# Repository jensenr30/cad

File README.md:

# Ryan's CAD Files (Schematics, PCBs, Simulations)

## kicad5
I started using KiCad 5.1.2 to draw schematics and lay out PCBs in May 2019.

## kicad4
I used KiCad 4.0.6 for 3 weeks in September 2017. The two projects I completed are:
* [Shift-Register Break-Out-Board](/kicad4/SRBOB) - A modular daisy-chain-able serial-in-parallel-out 74hc595-based shift register circuit board.
* [XPhone Input Board](/kicad4/XPhone/Input_Board) - A quad transducer amplifier and glockenspiel-key-hit-detection circuit board.

## eagle6
Eagle was the first CAD program I ever used. I started using Eagle (on version 5.11.0) sometime in early 2011. I stopped on version 6.6.0 in mid 2017.  Some of the more interesting projects I completed using Eagle are:
* [Analog Synth](eagle6/Analog%20Synth) - a bunch of analog (and digital) DIY synth modules.  Designed, built, and tested by your truly.  This includes VCOs, VCFs, VCAs, sequencers, front-panel designs, digital delay, manual oscillators, and power-distribution interconnect PCBs.
* [Stroboscope](eagle6/Stroboscope) - a device that can turn on and off LEDs very fast (at audio frequencies) in order to produce interesting/useful/helpful visual effects.  A stroboscope can be used to enable a human to monitor the rotation of things in real time, e.g. fans, drills, wheels, motors, spinning objects, guitar strings, and any other object engaged in cyclic motion.
* [VU Meter](eagle6/VU%20meter) - a circuit that represents audio amplitude vertically on several bargraphs (each bargraph displays the amplitude of a given section of the audio spectrum).  The device can be used to build a real-time visual audio spectrum analyzer.
* [FreqCount84](eagle6/FreqCount84) - Atmel microcontroller-based design for precise measurement of frequency of square waves.  I believe the hwardware & firmware achieved an accuracy of ± a few ppm with the help of a 1.5 pm TCXO.
* [9x9 LED Matrix](eagle6/9x9%20LED%20Matrix) - a 2D array of LEDs (9 LEDs wide, 9 LEDs tall).  I remember wanting to build an array that had an odd number of pixels because it would allow me to make symetric visual displays.  I programmed a game of pong for this 9x9 LED Matrix.  That code exists in [my repo for Arduino programs](https://github.com/jensenr30/Arduino/tree/master/_DISPLAY/9x9_LED_Matrix).
* [Prototype Boards](eagle6/Prototype%20Boards) - three PCBs that enable DIY circuit construction.  0.1"-arrays of SMD pads, 0.1"-arrays of through-holes, SOT-to-DIP break-out-boards, SOIC-to-DIP break-out-boards, etc...

## LTspice IV
I have used [LTspice](https://en.wikipedia.org/wiki/LTspice) version IV to simulate some of my circuits.

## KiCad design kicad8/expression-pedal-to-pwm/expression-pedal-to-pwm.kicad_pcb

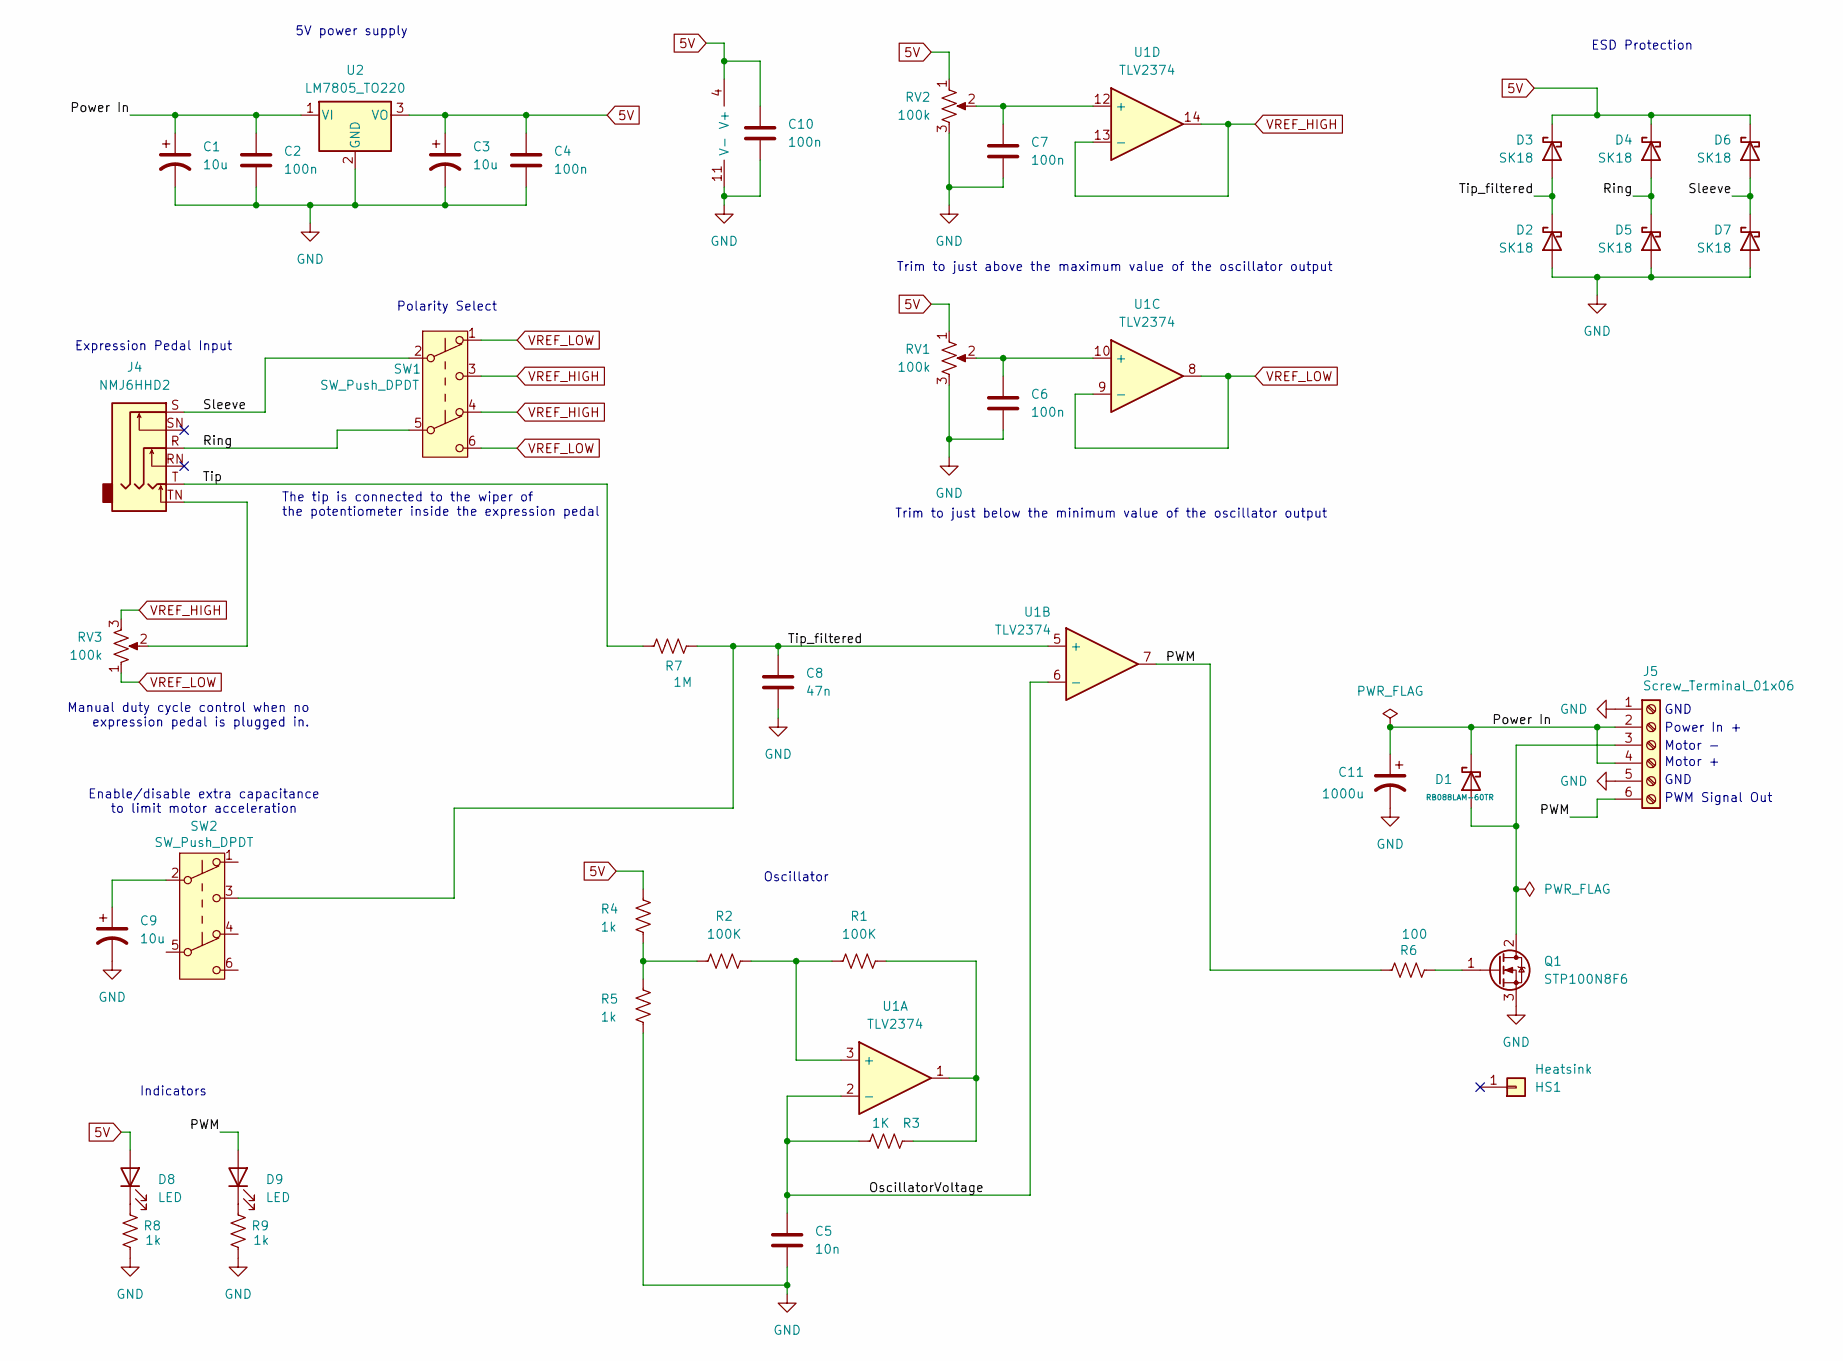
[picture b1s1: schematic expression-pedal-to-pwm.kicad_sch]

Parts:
C1, C3, C9: 10u; CP_Radial_D5.0mm_P2.50mm
C2, C4, C6, C7, C10: 100n; C_0603_1608Metric_Pad1.08x0.95mm_HandSolder
C5: 10n; C_0603_1608Metric_Pad1.08x0.95mm_HandSolder
C8: 47n; C_0603_1608Metric_Pad1.08x0.95mm_HandSolder
C11: 1000u; CP_Radial_D10.0mm_P5.00mm
D1: RB088LAM-60TR; D_SOD-128
D2, D3, D4, D5, D6, D7: SK18; D_SMA
D8, D9: LED; LED_D3.0mm_Horizontal_O3.81mm_Z6.0mm
HS1: Heatsink; Heatsink_Fischer_SK104-STCB_35x13mm__2xDrill3.5mm_ScrewM3
J4: NMJ6HHD2; Jack_6.35mm_Neutrik_NMJ6HHD2_Horizontal
J5: Screw_Terminal_01x06; TerminalBlock_MetzConnect_Type086_RT03406HBLC_1x06_P3.81mm_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
Q1: STP100N8F6; TO-220-3_Vertical
R1, R2: 100K; R_0603_1608Metric_Pad0.98x0.95mm_HandSolder
R3: 1K; R_0603_1608Metric_Pad0.98x0.95mm_HandSolder
R4, R5, R8, R9: 1k; R_0603_1608Metric_Pad0.98x0.95mm_HandSolder
R6: 100; R_0603_1608Metric_Pad0.98x0.95mm_HandSolder
R7: 1M; R_0603_1608Metric_Pad0.98x0.95mm_HandSolder
RV1, RV2: 100k; Potentiometer_Bourns_3296W_Vertical
RV3: 100k; Potentiometer_Piher_T-16H_Single_Horizontal
SW1, SW2: SW_Push_DPDT; SW_E-Switch_EG2219_DPDT_Angled
U1: TLV2374; SOIC-14_3.9x8.7mm_P1.27mm
U2: LM7805_TO220; TO-220-3_Vertical

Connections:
5V: C3.1, C4.1, C10.1, D3.1 (K), D4.1 (K), D6.1 (K), D8.2 (A), R4.2, RV1.1, RV2.1, U1.4 (V+), U2.3 (VO)
/OscillatorVoltage: C5.1, R3.2, U1.2 (-), U1.6 (-)
/PWM: D9.2 (A), J5.6, R6.1, U1.7
/Power In: C1.1, C2.1, C11.1, D1.1 (K), J5.2, J5.4, U2.1 (VI)
/Ring: D4.2 (A), D5.1 (K), J4.R, SW1.5 (B)
/Sleeve: D6.2 (A), D7.1 (K), J4.S, SW1.2 (B)
/Tip: J4.T, R7.2
/Tip_filtered: C8.1, D2.1 (K), D3.2 (A), R7.1, SW2.3 (C), U1.5 (+)
GND: C1.2, C2.2, C3.2, C4.2, C5.2, C6.2, C7.2, C8.2, C9.2, C10.2, C11.2, D2.2 (A), D5.2 (A), D7.2 (A), J5.1, J5.5, Q1.3 (S), R5.1, R8.1, R9.1, RV1.3, RV2.3, U1.11 (V-), U2.2 (GND)
unnamed: C9.1, SW2.2 (B)
unnamed: D1.2 (A), J5.3, Q1.2 (D)
unnamed: D8.1 (K), R8.2
unnamed: D9.1 (K), R9.2
unnamed: J4.TN, RV3.2
unnamed: Q1.1 (G), R6.2
unnamed: R1.2, R3.1, U1.1
unnamed: R2.1, R4.1, R5.2
unnamed: R1.1, R2.2, U1.3 (+)
unnamed: C6.1, RV1.2, U1.10 (+)
unnamed: C7.1, RV2.2, U1.12 (+)
VREF_HIGH: RV3.3, SW1.3 (C), SW1.4 (A), U1.13 (-), U1.14
VREF_LOW: RV3.1, SW1.1 (A), SW1.6 (C), U1.8, U1.9 (-)

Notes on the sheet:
ESD Protection
The tip is connected to the wiper of the potentiometer inside the expression pedal
GND
Power In +
Manual duty cycle control when no expression pedal is plugged in.
5V power supply
Indicators
Motor -
Motor +
Oscillator
Expression Pedal Input
PWM Signal Out
Trim to just above the maximum value of the oscillator output
Trim to just below the minimum value of the oscillator output
Polarity Select
Enable/disable extra capacitance to limit motor acceleration

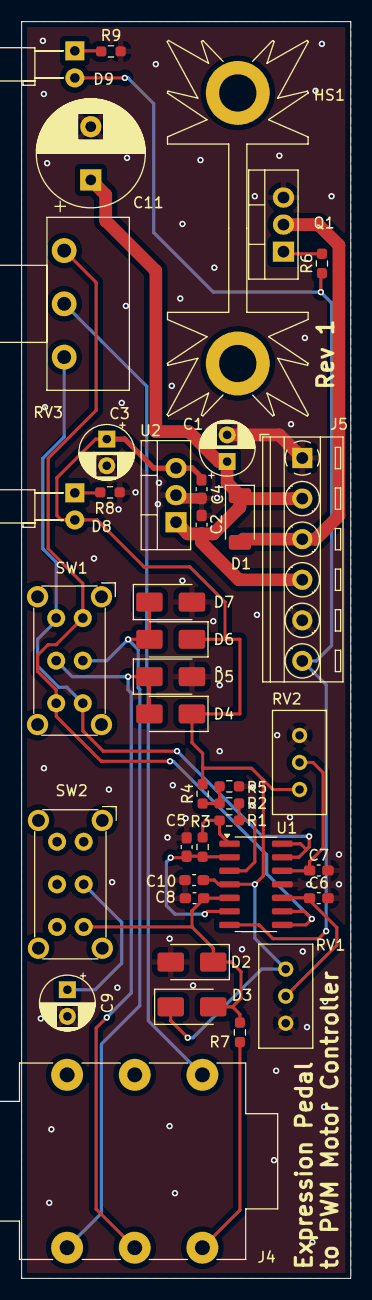
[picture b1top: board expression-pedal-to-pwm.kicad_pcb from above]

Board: 2 copper layers, 30.9 x 118.0 mm, 40 parts (0 on the bottom side), 22 nets.

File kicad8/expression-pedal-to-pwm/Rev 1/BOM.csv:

"Reference","Value","Datasheet","Footprint","Qty","DNP"
"C1  C3  C9","10u","~","Capacitor_THT:CP_Radial_D5.0mm_P2.50mm","3",""
"C2  C4  C6  C7  C10","100n","~","Capacitor_SMD:C_0603_1608Metric_Pad1.08x0.95mm_HandSolder","5",""
"C5","10n","~","Capacitor_SMD:C_0603_1608Metric_Pad1.08x0.95mm_HandSolder","1",""
"C8","47n","~","Capacitor_SMD:C_0603_1608Metric_Pad1.08x0.95mm_HandSolder","1",""
"C11","1000u","~","Capacitor_THT:CP_Radial_D10.0mm_P5.00mm","1",""
"D1","RB088LAM-60TR","~","Diode_SMD:D_SOD-128","1",""
"D2  D3  D4  D5  D6  D7","SK18","https://diotec.com/request/datasheet/sk12.pdf","Diode_SMD:D_SMA","6",""
"D8  D9","LED","~","LED_THT:LED_D3.0mm_Horizontal_O3.81mm_Z6.0mm","2",""
"HS1","Heatsink","https://www.mouser.com/datasheet/2/433/board-level-heatsink-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","Heatsink:Heatsink_Fischer_SK104-STCB_35x13mm__2xDrill3.5mm_ScrewM3","1",""
"J4","NMJ6HHD2","https://www.neutrik.com/en/product/nmj6hhd2","Connector_Audio:Jack_6.35mm_Neutrik_NMJ6HHD2_Horizontal","1",""
"J5","Screw_Terminal_01x06","~","TerminalBlock_MetzConnect:TerminalBlock_MetzConnect_Type086_RT03406HBLC_1x06_P3.81mm_Horizontal","1",""
"Q1","STP100N8F6","https://www.mouser.com/datasheet/2/389/stp100n8f6-1851325.pdf","Package_TO_SOT_THT:TO-220-3_Vertical","1",""
"R1  R2","100K","~","Resistor_SMD:R_0603_1608Metric_Pad0.98x0.95mm_HandSolder","2",""
"R3","1K","~","Resistor_SMD:R_0603_1608Metric_Pad0.98x0.95mm_HandSolder","1",""
"R4  R5  R8  R9","1k","~","Resistor_SMD:R_0603_1608Metric_Pad0.98x0.95mm_HandSolder","4",""
"R6","100","~","Resistor_SMD:R_0603_1608Metric_Pad0.98x0.95mm_HandSolder","1",""
"R7","1M","~","Resistor_SMD:R_0603_1608Metric_Pad0.98x0.95mm_HandSolder","1",""
"RV1  RV2  RV3","100k","~","-- mixed values --","3",""
"SW1  SW2","SW_Push_DPDT","~","Button_Switch_THT:SW_E-Switch_EG2219_DPDT_Angled","2",""
"U1","TLV2374","~","Package_SO:SOIC-14_3.9x8.7mm_P1.27mm","1",""
"U2","LM7805_TO220","https://www.onsemi.cn/PowerSolutions/document/MC7800-D.PDF","Package_TO_SOT_THT:TO-220-3_Vertical","1",""

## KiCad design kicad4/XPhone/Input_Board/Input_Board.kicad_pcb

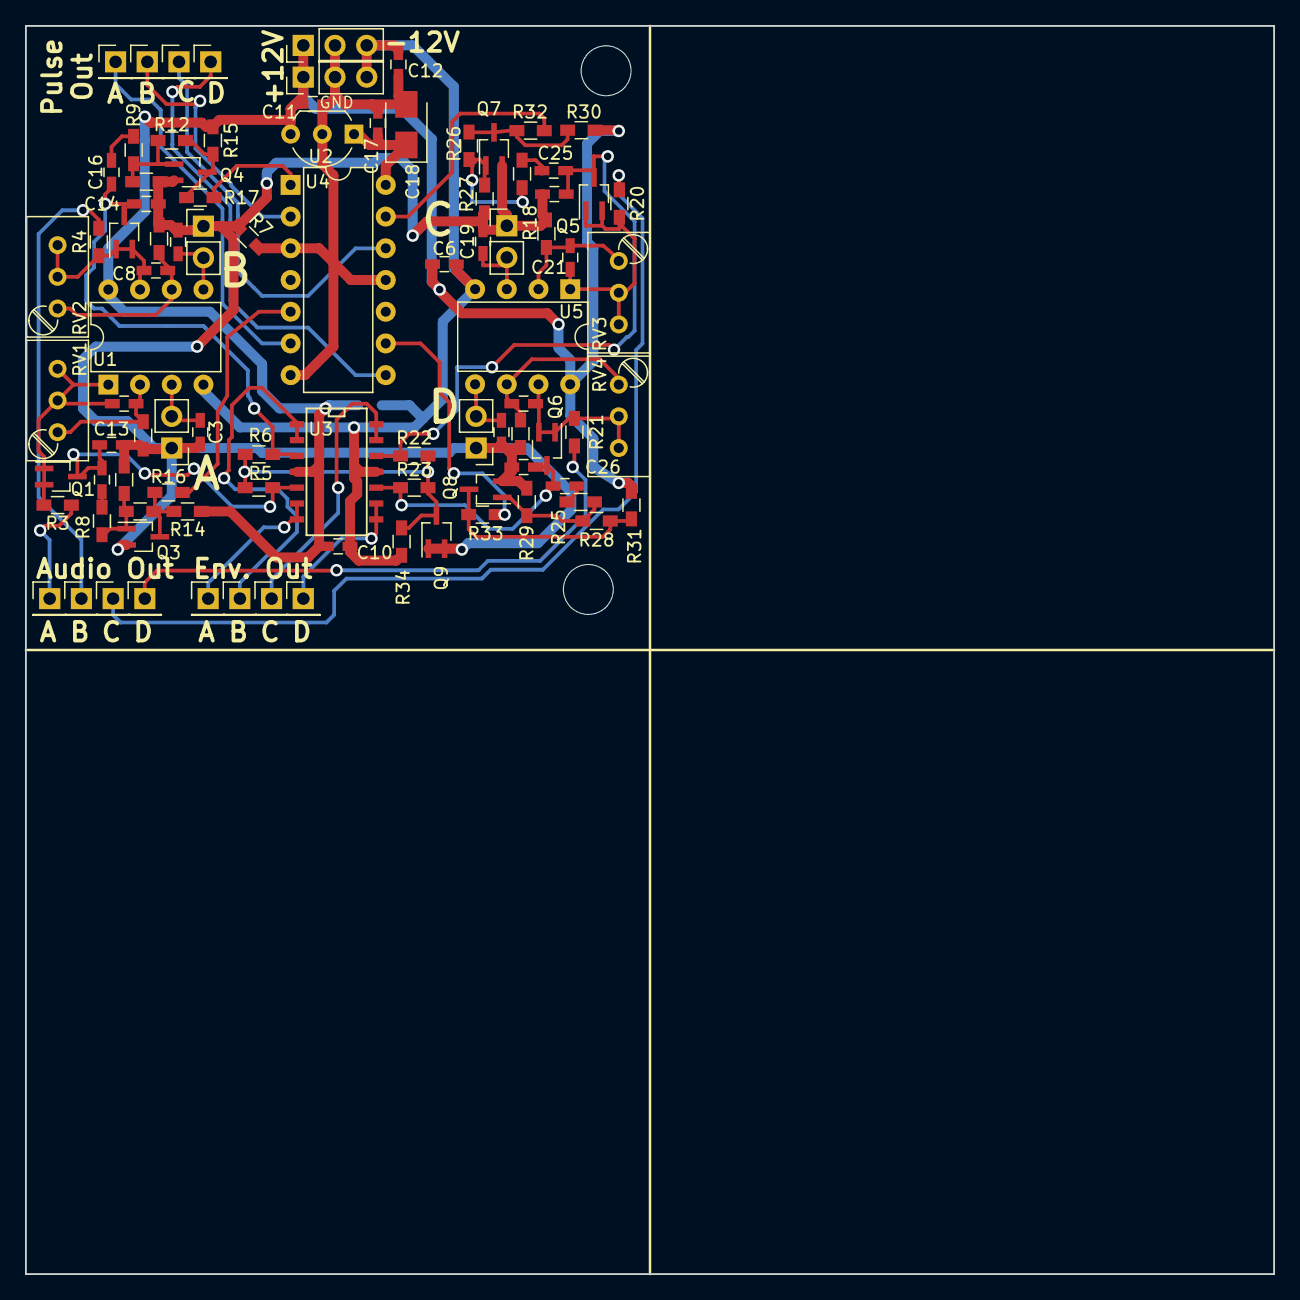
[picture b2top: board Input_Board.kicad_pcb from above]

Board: 2 copper layers, 100.0 x 100.0 mm, 93 parts (1 on the bottom side), 50 nets.

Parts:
C1, C3, C4, C6, C7, C8, C10, C11, C12, C13, C14, C15, C16, C17, C19, C20, C21, C22, C23, C24, C25, C26: 10n; C_0603_HandSoldering
C18: 10µ; CP_Tantalum_Case-B_EIA-3528-21_Wave
J1, J2, J7, J8: AUDIO; Pin_Header_Straight_1x01_Pitch2.54mm
J3, J4, J9, J10: ENV; Pin_Header_Straight_1x01_Pitch2.54mm
J5, J6, J11, J12: PULSE; Pin_Header_Straight_1x01_Pitch2.54mm
J13: Power In; Pin_Header_Straight_1x03_Pitch2.54mm
J14: Power Out; Pin_Header_Straight_1x03_Pitch2.54mm
L1, L2, L3, L4: Input Coil; Pin_Header_Straight_1x02_Pitch2.54mm
Q1, Q2, Q3, Q4, Q5, Q6, Q7, Q8, Q9: BC847CW; SOT-323_SC-70_Handsoldering
R1, R2, R18, R19: 4.7; R_0603_HandSoldering
R3, R4, R20, R21, R34: 10k; R_0603_HandSoldering
R5, R6, R10, R12, R22, R23, R26, R28: 10M; R_0603_HandSoldering
R7: 0; R_0603_HandSoldering
R8, R9, R11, R13, R24, R25, R27, R29: 1M; R_0603_HandSoldering
R14, R15, R16, R17, R30, R31, R32, R33: 100k; R_0603_HandSoldering
RV1, RV2, RV3, RV4: 10k; Potentiometer_Trimmer_Bourns_3296W
U1, U5: LM833; DIP-8_W7.62mm
U2: 78L05; TO-92_Inline_Wide
U3: TL084; SOIC-14_N
U4: 74HC14; DIP-14_W7.62mm

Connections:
+12V: C1.1, C6.1, C10.1, C11.1, J13.1, J14.1, R14.1, R15.1, R30.1, R31.1, U1.8, U2.3, U3.4, U5.8
-12V: C1.2, C6.2, C10.2, C12.2, J13.3, J14.3, R34.2, U1.4, U3.11, U5.4
GND: C11.2, C12.1, C17.2, C18.2, J13.2, J14.2, R7.2, U2.2, U4.3, U4.7, U4.11
GNDA: C3.2, C4.2, C13.2, C14.2, C19.2, C20.2, C23.2, C24.2, L1.1, L2.1, L3.1, L4.1, Q3.2, Q4.2, Q7.2, Q8.2, Q9.1, Q9.2, R1.2, R2.2, R7.1, R11.2, R13.2, R18.2, R19.2, R27.2, R29.2
unnamed: C3.1, L1.2, U1.3
unnamed: C4.1, L2.2, U1.5
unnamed: C7.1, Q1.1, Q1.2, R3.2, RV1.2, RV1.3, U1.1
unnamed: C7.2, R1.1, RV1.1, U1.2
unnamed: C8.1, Q2.1, Q2.2, R4.2, RV2.2, RV2.3, U1.7
unnamed: C8.2, R2.1, RV2.1, U1.6
unnamed: C13.1, C15.2, Q1.3, R5.1, U3.5
unnamed: C14.1, C16.2, Q2.3, R6.1, U3.3
unnamed: C15.1, R8.2
unnamed: C16.1, R9.2
unnamed: C19.1, L3.2, U5.3
unnamed: C20.1, L4.2, U5.5
unnamed: C21.1, Q5.1, Q5.2, R20.2, RV3.2, RV3.3, U5.1
unnamed: C21.2, R18.1, RV3.1, U5.2
unnamed: C22.1, Q6.1, Q6.2, R21.2, RV4.2, RV4.3, U5.7
unnamed: C22.2, R19.1, RV4.1, U5.6
unnamed: C23.1, C25.2, Q5.3, R22.1, U3.12
unnamed: C24.1, C26.2, Q6.3, R23.1, U3.10
unnamed: C25.1, R24.2
unnamed: C26.1, R25.2
unnamed: J1.1, R3.1
unnamed: J2.1, R4.1
unnamed: J3.1, U3.6, U3.7
unnamed: J4.1, U3.1, U3.2
unnamed: J5.1, U4.6
unnamed: J6.1, U4.2
unnamed: J7.1, R20.1
unnamed: J8.1, R21.1
unnamed: J9.1, U3.13, U3.14
unnamed: J10.1, U3.8, U3.9
unnamed: J11.1, U4.12
unnamed: J12.1, U4.8
unnamed: Q3.1, R8.1, R10.2, R11.1
unnamed: Q3.3, R10.1, R14.2, R16.2
unnamed: Q4.1, R9.1, R12.2, R13.1
unnamed: Q4.3, R12.1, R15.2, R17.2
unnamed: Q7.1, R24.1, R26.2, R27.1
unnamed: Q7.3, R26.1, R30.2, R32.2
unnamed: Q8.1, R25.1, R28.2, R29.1
unnamed: Q8.3, R28.1, R31.2, R33.2
unnamed: R16.1, U4.5
unnamed: R17.1, U4.1
unnamed: R32.1, U4.13
unnamed: R33.1, U4.9
VCC: C17.1, C18.1, U2.1, U4.14
V_ENV_BIAS: Q9.3, R5.2, R6.2, R22.2, R23.2, R34.1

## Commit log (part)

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2014-10-26 added pre-existing eagle schematics and libraries.
2014-11-16 Worked on the triangle wave part of the analog VCO.
2014-11-28 Working on analog synth stuff. Also just started the schematic for senior design (really just making the ATtiny24A symbol and package)
2015-01-23 added pad-per-hole strip protoype board, updated VCO v1, did some gerber stuff
2015-01-24 integrating EAGLE-6.6.0 stuff
2015-01-25 working on VCO-v1. optimizing circuit. removing resistors in favor of better pot placement.
2015-01-26 added reset circuitry to VCO-v1
2015-01-26 fixed capacitor values
2015-01-26 improved formatting of triangle->sine converter page (7)
2015-01-27 fixed stupid error with op amp inputs for frequency generation.
2015-01-31 fixed Reset LED configuration
2015-02-05 VCO-v1 had SOMETHING done to it. What was done, I know not.
2015-02-09 creating AR board (Attack/Release)
2015-02-15 added Attack-Release schematic with a JFET-based VCA that won't work. I will need to modify the schematic for a bual board.
2015-02-17 Added Voltage Controlled Amplifier v1. The thing actually works to some degree!!
2015-02-27 working on senior design circuit and pcb
2015-02-28 worked on the schematic
2015-03-04 working on VCA-v1
2015-03-04 Working on Power Distribution Board
2015-03-06 Working on VCA-v1 more. I need to add LED driving circuitry (LEDs, resistors, and a -5V source). Also, the silkscreen for the audio in/out jacks is on the back layer instead of the front. Fix this.
2015-03-07 working on VCA more. added caps to filter RF by shunting high frequencies to ground.
2015-03-07 "Finished" VCA-v1. Ordered PCBs from dirtypcbs.com.
2015-03-08 started schematic for analog switch. also changed a diode in a standard library
2015-03-09 revamped the analog switch circuit. two op amps, two transistors (a diode, and some resistors)
2015-03-13 Added a front panel for the Tri-Analog-Switch
2015-03-21 working on senior design and analog switch
2015-03-21 Updated the analog switch so that it doesn't suck so much. - Removed transistor and resistors. - Replaced with a diode to the gate of the JFET. - Changed grounding resistor from 330k to 56k. This was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
2015-03-23 working on VCA front panel.
    -CV at the top (with attenuation proceeded by offset adjustment)
    - Audio In in the middle (with attenuation)
    - Audio Out at the bottom.
2015-03-24 changed a single trace placement with the Senior Design project.(it was too close to the edge of the board) Also exported gerbers for OSHpark
2015-08-24 added a few things; rendered VCO-v1 pdf
2015-09-13 started echo chamber with eagle and kicad
2015-09-14 working on the Echo Chamber schematic; PT2399 was added to \!synth_sch library
2015-09-14 fixed little bug with the Echo Chamber schematic
2015-09-14 added some guide information to the schematic for the LEDs and the diodes, as well as referencing the data sheet as the source of the basic design of the PT2399 circuit
2015-09-20 I realized that I have more work to do on the schematic than I do have to do on the Panel. The circuit needs to be figured out exactly first. But that shouldn't take long. The filter may pose a sligh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
2015-10-10 working on VCO-v2 schematic; added a library part for CA3096 transistor array into that library that some other guy started
2015-10-10 VCO-v2 progress: linear voltage to exponential current converter and hysteresis circuit
2015-10-10 VCO-v2 high frequency compensation
2015-10-10 VCO-v2 - power supply. Also, I need to change those integration caps to be polarized types in the schematic and on the pcb...
2015-10-11 VCO-v2 PWM and Triangle outputs
2015-10-11 VCO-v2 PWM control voltage attenuation
2015-10-11 VCO-v2 Sine (from VCO-v1 basically)
2015-10-11 VCO-v2 LEDs sheet and signal names
2015-10-13 VCO-v2 - version 2.1 released! I changed a few things with the triangle-to-freq converter; I made the LEDs go into a bjt voltage source rather than the +5 V and -5 V regulated supplies, because conne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
2015-10-17 fixed error in VCO-v2 schematic - CV sum had a tuner going to -5 V instead of -9 V
2015-10-18 VCO-v2 - increased size of resistors around the triangle-wave x2 gain stage
2015-10-21 VCO-v2 improved readability
2015-10-24 VCO-v2.2 - updated an LED resistor value and exported PDF
2015-11-03 PS-VCO: created schematic
2015-11-03 PS-VCO creating PCB
2015-11-03 PS-VCO still working on PCB - making gerbers. proof reading. Need to add an LED for the CV signal
2015-11-03 PS-VCO added LED - organizing text on PCB
2015-11-06 Cigar Box Sequencer - created first draft of the front panel.
2015-11-08 CBS - Cigar Box Sequencer - 8 step - starting to put together a schematic for it
2015-11-08 CBS: moved file into folder
2015-11-09 CBS - still working on Cigar Box Sequencer schematic
2015-11-10 CBS - still working through Cigar Box Sequencer details
2015-11-14 CBS: working on skiimatic
2015-11-14 CBS: schematic (still)
2015-11-14 CBS: schematic (stillstill)
2015-11-14 CBS: chem and front panel of the cigar box
2015-11-14 CBS: added the switches for the GATE output that replaces the clock output
2015-11-15 CBS: updating schematic to make the GATE_OUT work properly
2015-11-15 CBS: generated pdf
2015-11-15 CBS: fixed output resistor values
2015-11-15 CBS: fixed output resistor values - other ones
2015-11-15 CBS: fixed output jack ground issue
2015-11-15 CBS: fixed the CV-OUT resistor value from 2.2k to 1k
2015-11-16 CBS: changed the binary input/output bypass connections so that the user cannot short the outputs of the 193 binary counter.
2015-11-16 CBS: added pdf documents
2015-11-26 added another prototype board type
2015-12-01 CBS: updating schematic and generating another pdf.
2015-12-01 CBS: fixed missing potentiometer value for output CV filter
2016-02-22 PS-VCO: updating documentation and schematic. rendered pdfs for schematic and pcb. generated a BOM
2016-02-25 updating PS-VCO. Changed a resistor value to get closer to 50% duty cycle. It is still very approximate, but before the duty cycle was around 25% or 30% or something really obviously not balanced.
2016-02-25 adding some data to the schematic
2016-02-26 updated a few PS-VCO things
2016-03-13 working on mixer; PS-VCO triple front panel
2016-03-19 working on Stroboscope
2016-03-19 stroboscope
2016-04-02 added a surface mount package to the ATtiny24A device
2016-04-23 FreqCount84 adding Input Stage (AC / DC coupling and Amplification); updated resistor and capacitor libraries so that the values and names are on the same side of the symbol rather than opposite sides
2016-04-25 added the FTDI USB->RS232 chip into the schematic because I am using it now.
2016-04-25 adding notes to FTDI RS232 chip.
2016-06-06 adding VCA-v2 initial stuff to the repo. SCH is not really created yet, I just copied VCA-v1
2016-06-07 created VCA-v2 schematic. PCB exists, but it is not layed out or routed
2016-06-11 added DMMT3904W to part library in synth_sch; making progress on VCA-v2 layout
2016-06-11 making progress on VCA-v2. Updated the Eurorack power connector
2016-06-11 making some progress on VCA-v2
2016-06-11 VCA-v2. Using eagle version 7.6 to generate the gerbers because my install of version 6 was having trouble finding its output devices... whatever that means...
2016-06-12 organizing VCA-v2 stuff; pdf
2016-06-12 updating text placement and generating the assembly drawings for computer reference and for printing
2016-06-18 making progress on a breakout board
2016-06-18 finished laying out the breakout board. going to order this soon.
2016-06-29 prototype board gerbers; ScreamFilter
2016-07-08 nothing
2016-07-11 VCA-v2 new schematic pdf; ScreamFilter layout has begun.
2016-07-13 working on ScreamFilter layout. close to finished
2016-07-15 working on ScreamFilter DIY layout
2017-07-06 added .gitignore
2017-07-06 updated .gitignore to include _autosave- files
2017-07-06 removing the autosave file in SRBOB
2017-07-06 updating SRBOB project
2017-07-06 minor modification to XPhone Input Board
2017-07-09 forgot to save XPhone/Input_Board project file
2017-07-14 ^XPhone Input Board layout; +bug record
2017-07-14 +pdf of schematic for XPhone/Input_Board
2017-07-14 XPhone/Input_Board components are roughly organized
2017-07-14 XPhone/Input_Board +power connectors
2017-07-15 XPhone/Input_Board
2017-07-15 made tl084 a SOIC and returned 74hc14 back to a DIP
2017-07-19 XPhone/Input_Board - placed parts around L3 amplifier
2017-07-19 XPhone/Input_Board - laid traces for parts around L3
2017-07-19 fixed -12V symbol (used to have +12V pin name which automatically connected it with the +12 V supply. BAD. Updated XPhone/Input_Board too
2017-07-19 XPhone/Input_Board touching-up first layout of amplifier circuit
2017-07-20 ignoring the modules I add
2017-07-20 updating transistor REF** in XPhone/Input_Board
2017-07-20 XPhone/Input_Board L4 circuit
2017-07-20 XPhone/Input_Board ^layout; using wide TO-92; close to done
2017-07-20 XPhone/Input_Board - just realized I forgot to add V_ENV_BIAS to the circuit; continuing layout...
2017-07-20 XPhone/Input_Board finished laying out everything of importance (except the V_ENV_BIAS\!
2017-07-20 XPhone/Input_Board removing unnecessary caps
2017-07-20 XPhone/Input_Board .pro file
2017-07-20 XPhone/Input_Board fixed L orientation (not a big deal, but it bugged me)
2017-07-22 XPhone/Input_Board +ENV_BIAS to circuit
2017-07-22 V_ENV_BIAS
2017-07-22 polishing the F.Fab layer
2017-07-22 working on silscreen
2017-07-22 XPhone TODO list
2017-07-24 XPhone/Input_Board +mounting holes; ^silkscreen; +bug picture
2017-07-25 XPhone/Input_Board ^PCB; +2x2 Panel
2017-07-25 fixed generation of panel
2017-07-25 initial panel gerbers - not ready yet
2017-07-26 XPhone/Input Board
2017-07-26 optimizing XPhone/Input Board layout for cutting it into pieces; traces routed not so close to the board
2017-07-26 creating panel and gerbers
2017-07-26 made a panel gerber package for dirtypcbs
2019-05-04 deleted: references, bugs, and Test_Project
2019-05-04 Preparing for merge with other CAD program files... <<{KiCad 4}>>
2019-05-04 PS-VCO, ScreamFilter, VCA-v2, and XPhone stuff. (something I must have done 2 years ago...)
2019-05-04 Preparing for merge with other CAD program files... <<{Eagle 6.6.0}>>
2019-05-04 setting up a README.md for CAD repo
2019-05-04 rendering PDFs of old schematics to ensure information is not difficult to access later on...; deleting some useless old projects.
2019-05-04 organizing eagle6/Synth folder - deleting some old junk...
2019-05-04 eagle6: renamed Sequencer -> 8-Note Sequencer; organizing misc files...
2019-05-04 eagle6: rendering old schematics...
2019-05-04 renamed: Strobeoscope -> Stroboscope
2019-05-04 README.md: changed "VU Meter" to "VU meter" (lowercase m)
    This is linux-type stuff, my man; the case of the letter matters.
2019-05-04 adding LTspice IV simulation files to the repo
2019-05-04 README.md: added section about LTspice IV
2019-05-04 + inverter XOR noise generator pics
2019-05-04 LTspice IV: adding a simple solenoid switching simulation
2019-08-12 + magnetoscope project (almost nothing - just an inductor on a blank schematic at this point)
2022-06-16 adding FreeCad and Silent Susan project
2022-06-16 adding kicad magnetoscope from 2 years ago
2022-06-17 silent susan v5.5 - fixed bolt hole; got Path looking good; generate first G-code; added G-code cheat sheet web page"
2022-06-18 created g-code for base
2022-06-19 changed washer clearance to 100 thou on each side to avoid interference.
2022-06-20 created silent susan v6 based on dad's design
2022-06-20 silent susan v6
2022-08-19 putting together spreadsheet for parameteric definition of napkin holder
2022-08-19 napkin holder v3 CAD and g-code
2022-08-21 created napkin holder v2.2
2022-08-26 fixed napkin holder 2.2
2023-03-26 cabinet side holes
2024-07-27 Created expression-pedal-to-pwm schematic
2024-07-29 Expression-Pedal-to-PWM - make schematic 8.5x11 in
2024-07-31 Layout components and traces for Expression Pedal PWM Motor Controller
2024-07-31 Add copper pour and via stitching to Expression-Pedal-to-PWM
2024-07-31 Export Rev 1 Expression Pedal to PWM
2024-08-20 Add fixed TerminalBlock_MetzConnect footprints
2024-08-20 Fix expression pedal Terminal Block
2025-10-11 Add wisconsin silhouette
